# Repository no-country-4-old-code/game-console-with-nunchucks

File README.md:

# Simple Game Console Based on AtMega87-20PU
This is a minimal gaming console based on two AtMega-MCUs.
The input is done via two old "Wii"-Nunchucks.
Output is given via monitor (VGA) and scores are displayed via 7-segment-displays.

The whole thing is rather old (2013), but I had a lot of fun building it.
In other words: Do not expect much regarding clean code etc.

I translate the original documentation into english using AI and put it below.
And yes.. I did a documentation.. but only because this was needed to publish the project on Heise.
The original documentation with all the nice pictures is also in the repo.

## Documentation (Translated by AI)

## Project Overview

This repository documents a simple video game console that runs the classic game **"Pong"** on a standard VGA monitor, controlled by two Wii Nunchuks. The hardware is powered by just two AtMega88-20PU microcontrollers, and the implementation showcases the technical challenges of VGA signal generation and game logic with limited resources.

## Features

**VGA Output**  
The console directly drives a VGA monitor in 640×480 @60Hz mode, outputting all graphics using the AtMega88 microcontroller. The graphics pipeline and Pong gameplay logic are written in Assembler for maximum performance.

**Controller Support**  
Two original Wii Nunchuks serve as input devices. Their joysticks and accelerometers allow paddle control, selectable via board jumpers. Communication is handled via I²C/TWI.

**Score Display**  
An array of four seven-segment displays shows the current score. Multiplexing and updates are managed in C, running on the second AtMega.

**Additional Controls**  
The board features jumpers for color/mode selection, a reset/start button, and three output pins as triggers for a simple sound system (optional, not included).

**Efficient Communication**  
The microcontrollers communicate via a custom UART protocol for fast score and control updates.

## Technical Highlights

### VGA Module

This unit is responsible for image generation, VGA signaling, game mechanics, and data transfer to the controller module. With the VGA protocol being extremely timing-sensitive, the implementation uses Assembler and overclocks the AtMega88 to 22.1145 MHz.  
The software architecture separates graphics generation (run at 5.5 MHz "pixel clock") and game logic into distinct processes, with a timer ISR acting as the scheduler.

### Controller Module

Implemented in C, this module polls the Nunchuks, manages scores, updates the seven-segment displays, and coordinates with the VGA module via UART. Nunchuk polling and game state updates are all performed within a single frame to maintain responsiveness.

### Hardware Design

Most circuit details are derived from the AtMega88 datasheet and well-known application notes (e.g., Philips AN97055 for level shifting). Special consideration is given to transistor pin layouts, with corrective diagrams provided for BC640 and BS108 variants.

## Notes on VGA Implementation

- **Pixel Clock Limitations:** The microcontroller cannot match the standard 25 MHz VGA pixel clock. Instead, output occurs at roughly 5.5 MHz, resulting in horizontally stretched pixels—but reliable display.
- **Memory Handling:** Graphics data is loaded into SRAM at startup for fast access; worklines and images are organized for efficient redrawing of game elements.
- **UART Datagram:** The UART protocol is custom-designed, using 8 data bits, one stop bit, and a baud rate of 32,143 Kbps.

## Images & Schematics

Key diagrams illustrating VGA timing, connector layouts, software architecture, datagram structure, and transistor pinouts are included in the documentation.

---

### Author

**Moritz Koal** (2013)

---

## Caution on Hardware Layout

When assembling, pay close attention to transistor pin assignments—especially for BC640 (swap collector and base) and BS108 (rotate drain and source by 180°). Refer to the included diagrams and datasheets for exact orientation.

---

## License

Feel free to modify, share, and build upon this project for educational or personal use.

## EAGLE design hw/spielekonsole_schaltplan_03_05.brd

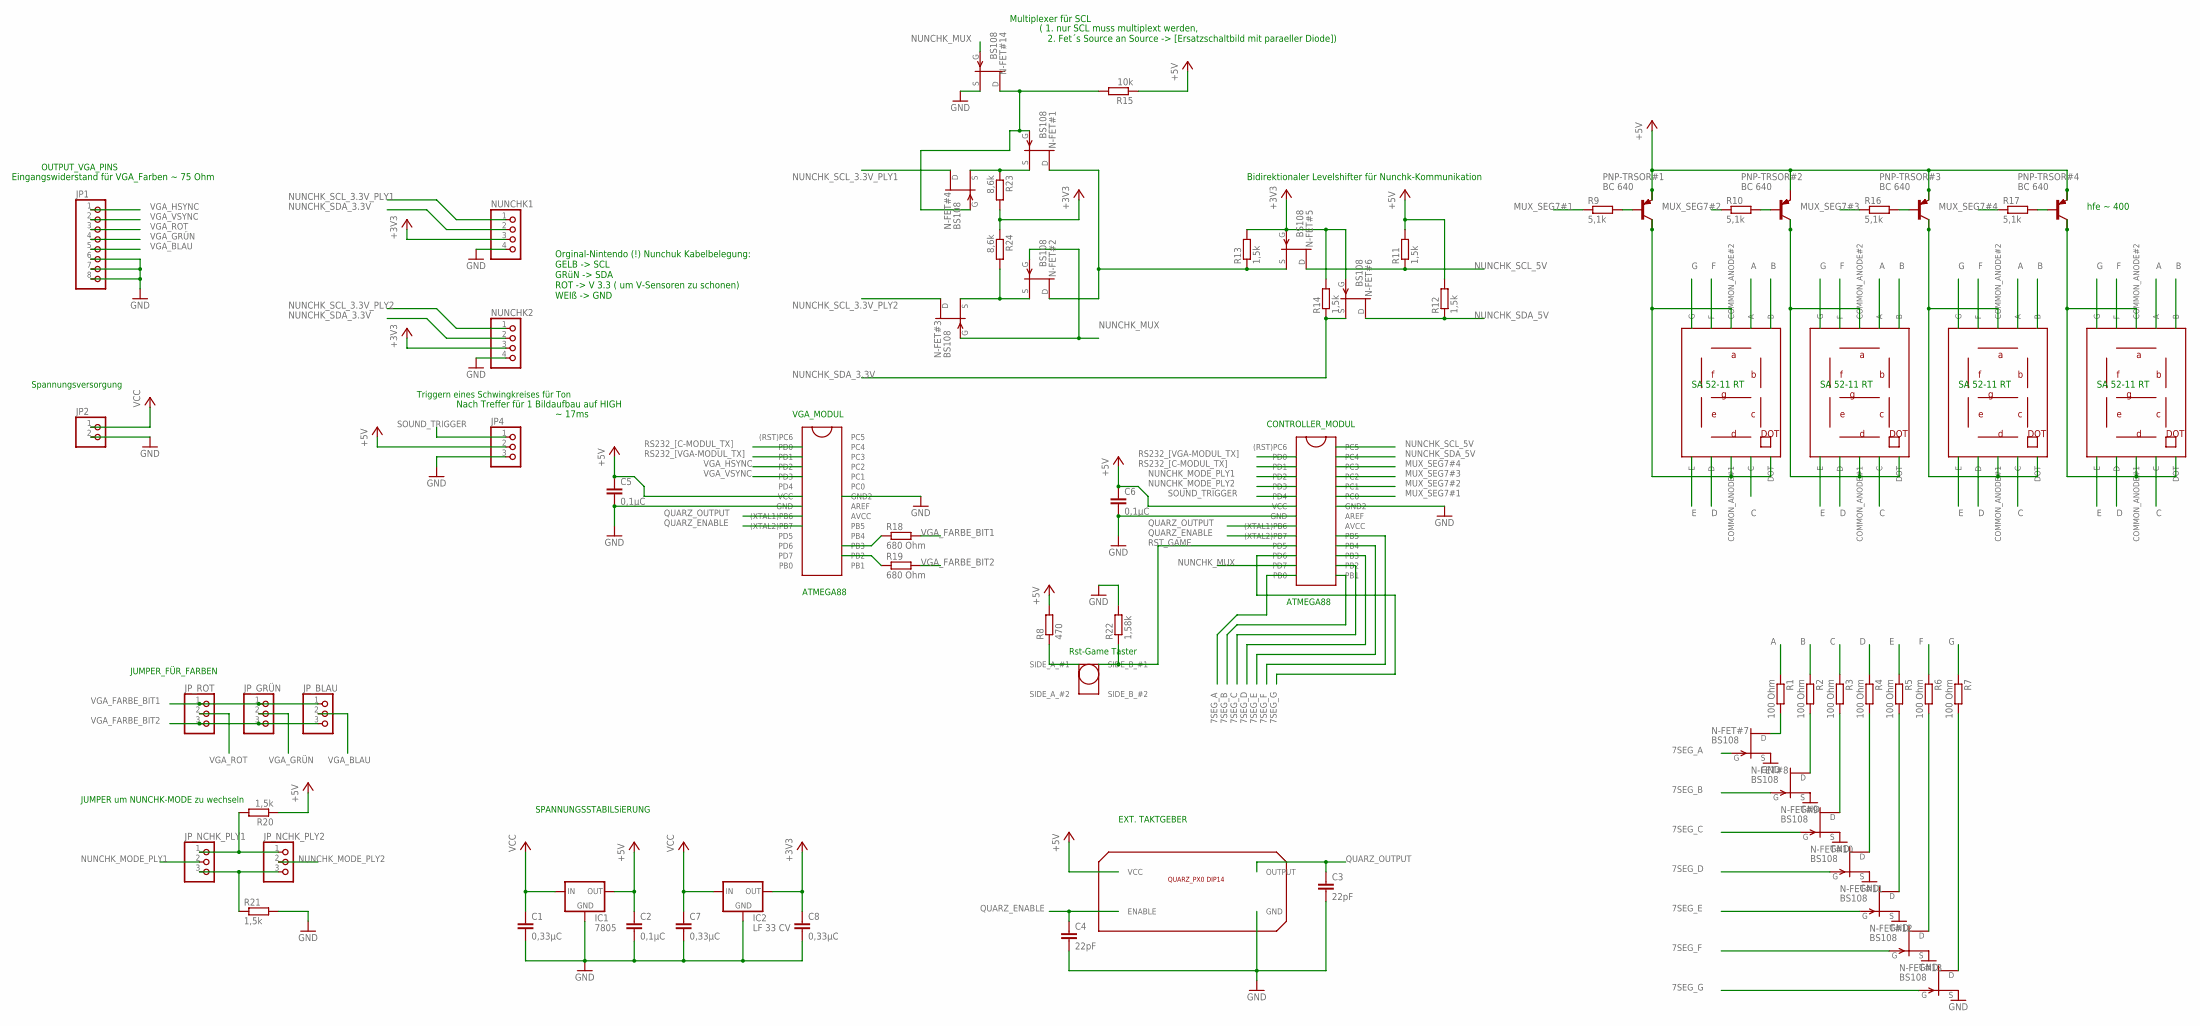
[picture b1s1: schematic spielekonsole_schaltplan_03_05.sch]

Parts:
C1, C7, C8: 0,33µC; C025-024X044
C2, C5, C6: 0,1µC; C025-024X044
C3, C4: 22pF; C025-024X044
IC1: 7805; 78XXL
IC2: LF 33 CV; 78XXL
JP1: PINHD-1X8; 1X08
JP2: PINHD-1X2; 1X02
JP4: PINHD-1X3; 1X03
JP_BLAU: PINHD-1X3; 1X03
JP_GRÜN: PINHD-1X3; 1X03
JP_NCHK_PLY1, JP_NCHK_PLY2: PINHD-1X3; 1X03
JP_ROT: PINHD-1X3; 1X03
N-FET#1, N-FET#2, N-FET#3, N-FET#4, N-FET#5, N-FET#6, N-FET#7, N-FET#8, N-FET#9, N-FET#10, N-FET#11, N-FET#12, N-FET#13, N-FET#14: BS108; TO92
NUNCHK1, NUNCHK2: PINHD-1X4; 1X04
PNP-TRSOR#1, PNP-TRSOR#2, PNP-TRSOR#3, PNP-TRSOR#4: BC 640; TO92-CBE
R1, R2, R3, R4, R5, R6, R7: 100 Ohm; 0204/7
R8: 470; 0204/7
R9, R10, R16, R17: 5,1k; 0204/7
R11, R12, R13, R14, R20, R21: 1,5k; 0204/7
R15: 10k; 0204/7
R18, R19: 680 Ohm; 0204/7
R22: 1,58k; 0204/7
R23, R24: 8,6k; 0204/7
U$1, U$2: ATMEGA 88-20 PU; ATMEGA8_PAC
U$3: QUARZ_PX0_DIP14; QUARZ_PX0_DIP14_PAC
U$4, U$5, U$6, U$7: SA 52-11 RT; SIEBEN_SEG_SA52-11_PAC
U$8: TASTER_1; TASTER_1_PAC

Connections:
7SEG_A: N-FET#7.2 (G), U$2.PB0
7SEG_B: N-FET#8.2 (G), U$2.PB1
7SEG_C: N-FET#9.2 (G), U$2.PB2
7SEG_D: N-FET#10.2 (G), U$2.PB3
7SEG_E: N-FET#11.2 (G), U$2.PB4
7SEG_F: N-FET#12.2 (G), U$2.PB5
7SEG_G: N-FET#13.2 (G), U$2.PD6
+3V3: C8.1, IC2.OUT, N-FET#5.2 (G), N-FET#6.2 (G), NUNCHK1.3, NUNCHK2.3, R13.2, R14.2, R23.2, R24.1
+5V: C2.1, C5.1, C6.1, IC1.OUT, JP4.2, PNP-TRSOR#1.E, PNP-TRSOR#2.E, PNP-TRSOR#3.E, PNP-TRSOR#4.E, R8.2, R11.2, R12.2, R15.1, R20.1, U$1.VCC, U$2.VCC, U$3.VCC
A: R1.1, U$4.A, U$5.A, U$6.A, U$7.A
B: R2.1, U$4.B, U$5.B, U$6.B, U$7.B
C: R3.1, U$4.C, U$5.C, U$6.C, U$7.C
D: R4.1, U$4.D, U$5.D, U$6.D, U$7.D
E: R5.1, U$4.E, U$5.E, U$6.E, U$7.E
ENABLE_SEG7#1: PNP-TRSOR#1.C, U$4.COMMON_ANODE#1, U$4.COMMON_ANODE#2, U$4.DOT
ENABLE_SEG7#2: PNP-TRSOR#2.C, U$5.COMMON_ANODE#1, U$5.COMMON_ANODE#2, U$5.DOT
ENABLE_SEG7#3: PNP-TRSOR#3.C, U$6.COMMON_ANODE#1, U$6.COMMON_ANODE#2, U$6.DOT
ENABLE_SEG7#4: PNP-TRSOR#4.C, U$7.COMMON_ANODE#1, U$7.COMMON_ANODE#2, U$7.DOT
F: R6.1, U$4.F, U$5.F, U$6.F, U$7.F
G: R7.1, U$4.G, U$5.G, U$6.G, U$7.G
GND: C1.2, C2.2, C3.2, C4.2, C5.2, C6.2, C7.2, C8.2, IC1.GND, IC2.GND, JP1.6, JP1.7, JP1.8, JP2.2, JP4.3, N-FET#7.3 (S), N-FET#8.3 (S), N-FET#9.3 (S), N-FET#10.3 (S), N-FET#11.3 (S), N-FET#12.3 (S), N-FET#13.3 (S), N-FET#14.3 (S), NUNCHK1.4, NUNCHK2.4, R21.2, R22.2, U$1.GND1 (GND), U$1.GND2, U$2.GND1 (GND), U$2.GND2, U$3.GND
MUX_SEG7#1: R9.1, U$2.PC0
MUX_SEG7#2: R10.1, U$2.PC1
MUX_SEG7#3: R16.1, U$2.PC2
MUX_SEG7#4: R17.1, U$2.PC3
unnamed: R8.1, U$8.SIDE_A_#1
unnamed: PNP-TRSOR#1.B, R9.2
unnamed: PNP-TRSOR#2.B, R10.2
unnamed: PNP-TRSOR#3.B, R16.2
unnamed: PNP-TRSOR#4.B, R17.2
unnamed: R18.1, U$1.PB3
unnamed: R19.1, U$1.PB2
unnamed: JP_NCHK_PLY1.3, JP_NCHK_PLY2.3, R21.1
unnamed: N-FET#1.2 (G), N-FET#4.2 (G), N-FET#14.1 (D), R15.2
unnamed: JP_NCHK_PLY1.1, JP_NCHK_PLY2.1, R20.2
unnamed: N-FET#1.1 (D), N-FET#2.1 (D), N-FET#5.3 (S), R13.1
unnamed: N-FET#1.3 (S), N-FET#4.3 (S), R23.1
unnamed: N-FET#2.3 (S), N-FET#3.3 (S), R24.2
unnamed: N-FET#7.1 (D), R1.2
unnamed: N-FET#8.1 (D), R2.2
unnamed: N-FET#9.1 (D), R3.2
unnamed: N-FET#10.1 (D), R4.2
unnamed: N-FET#11.1 (D), R5.2
unnamed: N-FET#12.1 (D), R6.2
unnamed: N-FET#13.1 (D), R7.2
NUNCHK_MODE_PLY1: JP_NCHK_PLY1.2, U$2.PD2
NUNCHK_MODE_PLY2: JP_NCHK_PLY2.2, U$2.PD3
NUNCHK_MUX: N-FET#2.2 (G), N-FET#3.2 (G), N-FET#14.2 (G), U$2.PD7
NUNCHK_SCL_3.3V_PLY1: N-FET#4.1 (D), NUNCHK1.1
NUNCHK_SCL_3.3V_PLY2: N-FET#3.1 (D), NUNCHK2.1
NUNCHK_SCL_5V: N-FET#5.1 (D), R11.1, U$2.PC5
NUNCHK_SDA_3.3V: N-FET#6.3 (S), NUNCHK1.2, NUNCHK2.2, R14.1
NUNCHK_SDA_5V: N-FET#6.1 (D), R12.1, U$2.PC4
QUARZ_ENABLE: C4.1, U$1.PB7 ((XTAL2)PB7), U$2.PB7 ((XTAL2)PB7), U$3.ENABLE
QUARZ_OUTPUT: C3.1, U$1.PB6 ((XTAL1)PB6), U$2.PB6 ((XTAL1)PB6), U$3.OUTPUT
RS232_[C-MODUL_TX]: U$1.PD0, U$2.PD1
RS232_[VGA-MODUL_TX]: U$1.PD1, U$2.PD0
RST_GAME: R22.1, U$2.PD5, U$8.SIDE_B_#1
SOUND_TRIGGER: JP4.1, U$2.PD4
VCC: C1.1, C7.1, IC1.IN, IC2.IN, JP2.1
VGA_BLAU: JP1.5, JP_BLAU.2
VGA_FARBE_BIT1: JP_BLAU.1, JP_GRÜN.1, JP_ROT.1, R18.2
VGA_FARBE_BIT2: JP_BLAU.3, JP_GRÜN.3, JP_ROT.3, R19.2
VGA_GRÜN: JP1.4, JP_GRÜN.2
VGA_HSYNC: JP1.1, U$1.PD2
VGA_ROT: JP1.3, JP_ROT.2
VGA_VSYNC: JP1.2, U$1.PD3

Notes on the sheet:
OUTPUT_VGA_PINS
JUMPER_FÜR_FARBEN
VGA_MODUL
SPANNUNGSSTABILSiERUNG
Spannungsversorgung
EXT. TAKTGEBER
CONTROLLER_MODUL
ATMEGA88
JUMPER um NUNCHK-MODE zu wechseln
Triggern eines Schwingkreises für Ton
Rst-Game Taster
Orginal-Nintendo (!) Nunchuk Kabelbelegung: GELB -> SCL GRüN -> SDA ROT -> V 3.3 ( um V-Sensoren zu schonen) WEIß -> GND
Multiplexer für SCL
Bidirektionaler Levelshifter für Nunchk-Kommunikation
hfe ~ 400
Eingangswiderstand für VGA_Farben ~ 75 Ohm
Nach Treffer für 1 Bildaufbau auf HIGH
~ 17ms
( 1. nur SCL muss multiplext werden, 2. Fet´s Source an Source -> [Ersatzschaltbild mit paraeller Diode])
SA 52-11 RT

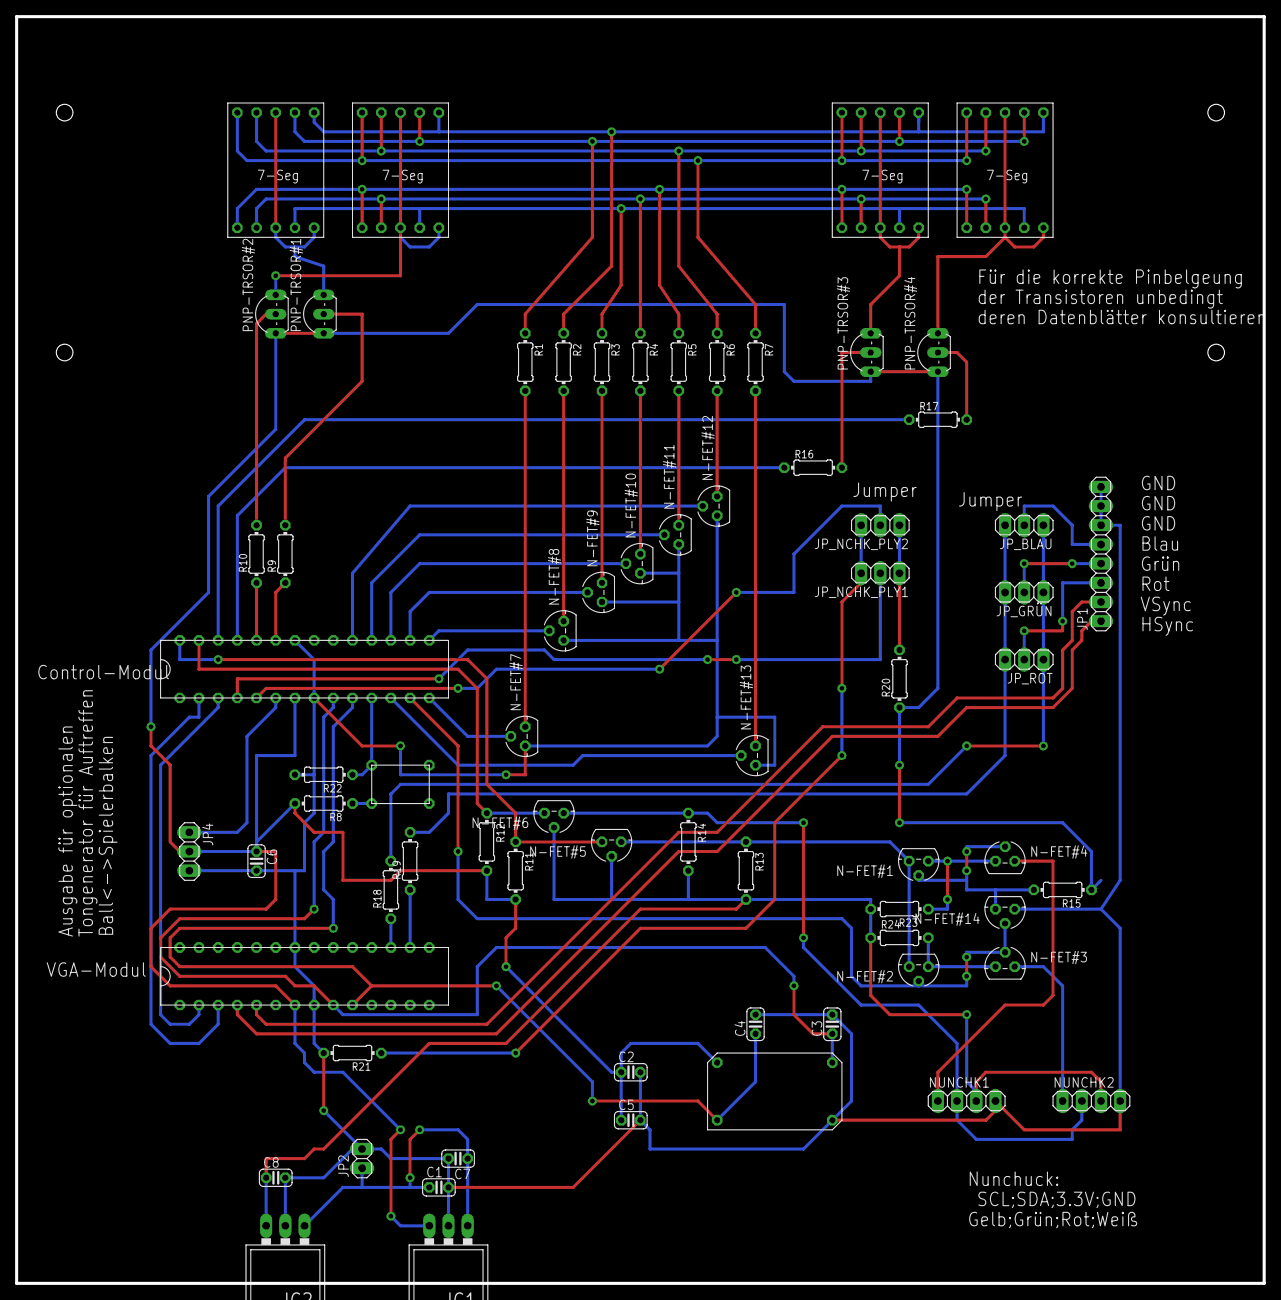
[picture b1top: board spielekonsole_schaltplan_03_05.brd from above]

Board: 2 copper layers, 165.1 x 167.6 mm, 70 parts (0 on the bottom side), 67 nets.

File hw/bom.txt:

Stückliste

//======== Eagle

Qty Value            Device             Package                Parts                                                                                                                             Description                
1                    PINHD-1X2          1X02                   JP2                                                                                                                               PIN HEADER                 
6                    PINHD-1X3          1X03                   JP4, JP_BLAU, JP_GRÜN, JP_NCHK_PLY1, JP_NCHK_PLY2, JP_ROT                                                                         PIN HEADER                 
2                    PINHD-1X4          1X04                   NUNCHK1, NUNCHK2                                                                                                                  PIN HEADER                 
1                    PINHD-1X8          1X08                   JP1                                                                                                                               PIN HEADER                 
3   0,1µC            C-EU025-024X044    C025-024X044           C2, C5, C6                                                                                                                        CAPACITOR, European symbol 
3   0,33µC           C-EU025-024X044    C025-024X044           C1, C7, C8                                                                                                                        CAPACITOR, European symbol 
1   1,58k            R-EU_0204/7        0204/7                 R22                                                                                                                               RESISTOR, European symbol  
6   1,5k             R-EU_0204/7        0204/7                 R11, R12, R13, R14, R20, R21                                                                                                      RESISTOR, European symbol  
7   100 Ohm          R-EU_0204/7        0204/7                 R1, R2, R3, R4, R5, R6, R7                                                                                                        RESISTOR, European symbol  
1   10k              R-EU_0204/7        0204/7                 R15                                                                                                                               RESISTOR, European symbol  
2   22pF             C-EU025-024X044    C025-024X044           C3, C4                                                                                                                            CAPACITOR, European symbol 
1   470              R-EU_0204/7        0204/7                 R8                                                                                                                                RESISTOR, European symbol  
4   5,1k             R-EU_0204/7        0204/7                 R9, R10, R16, R17                                                                                                                 RESISTOR, European symbol  
2   680 Ohm          R-EU_0204/7        0204/7                 R18, R19                                                                                                                          RESISTOR, European symbol  
1   7805             78XXL              78XXL                  IC1                                                                                                                               VOLTAGE REGULATOR          
2   8,6k             R-EU_0204/7        0204/7                 R23, R24                                                                                                                          RESISTOR, European symbol  
2   ATMEGA 88-20 PU  ATMEGA8            ATMEGA8_PAC            U$1, U$2                                                                                                                                                     
4   BC 640           2N4126             TO92-CBE               PNP-TRSOR#1, PNP-TRSOR#2, PNP-TRSOR#3, PNP-TRSOR#4                                                                                PNP Transistror            
14  BS108            2N3819             TO92                   N-FET#1, N-FET#2, N-FET#3, N-FET#4, N-FET#5, N-FET#6, N-FET#7, N-FET#8, N-FET#9, N-FET#10, N-FET#11, N-FET#12, N-FET#13, N-FET#14 N-Channel Junction FET     
1   LF 33 CV         78XXL              78XXL                  IC2                                                                                                                               VOLTAGE REGULATOR          
1   QUARZ_PX0_DIP14  QUARZ_PX0_DIP14    QUARZ_PX0_DIP14_PAC    U$3                                                                                                                                                          
4   SA 52-11 RT      SIEBEN_SEG_SA52-11 SIEBEN_SEG_SA52-11_PAC U$4, U$5, U$6, U$7                                                                                                                                           
1   TASTER_1         TASTER_1           TASTER_1_PAC           U$8                                                                                                                                                          

//========== Sonstiges 

2  *	GS 28P-S		IC-Sockel für Atmega88
5  *	MPE 087-1-003		Stiftleisten mit 2,54mm ( für Jumper )
5  *	Jumper 2,54mm		Zur Auswahl Joystick/Beschleunigungssensor etc
8  *	MPE 094-1-005		Buchsenleiste,1X05 2,54mm für Siebensegment Blöcke
4  *	MPE 094-1-004		Buchsenleiste,1X04 2,54mm für Quarz und Nunchucks
2  *	MPE 087-1-004		Stiftleiste,1X04 2,54mm für Nunchucks ( Besser wäre natürlich ein Adapter, so dass man die Nunchucks nicht aufschneiden muss )
1  *	Tastschalter + gegebenfalls entsprechende Buchsenleisten ( z.B. FSM2JH + 2* MPE 094-1-003 )
1  * 	DELOCK 65170		16 Pin, VGA-Buchse <-> Terminalblock. ( Erleichtert den Anschluss )

//========== Stromversorgung
1  *	PSAA 18U-090		Kompaktschaltnetzteil , 18 W , 9 V out
1  *	HEBFL 21		Hohlstecker-Einbaubuchse, Flansch, Stift 2,1mm

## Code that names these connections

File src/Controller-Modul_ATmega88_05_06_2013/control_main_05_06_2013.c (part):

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#define RST_PORT PORTD
#define RST_PINS PIND
#define RST_DDR DDRD
#define RST_PIN PD5
#define RST_ACTIV 1 // High Aktiv

// Watchdog
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#define NUNCHK_MODE_PORT PORTD
#define NUNCHK_MODE_PINS PIND
#define NUNCHK_MODE_DDR DDRD
#define NUNCHK_MODE_PIN_PLY1 PD2
#define NUNCHK_MODE_PIN_PLY2 PD3
#define NUNCHK_MODE_STICK 1
#define NUNCHK_MODE_VSENSOR 0
#define NUNCHK_MODE_STICK_SEGMENT 0
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// 'Pong'-Ton Ausgabe
#define SOUND_PORT PORTD
#define SOUND_DDR DDRD
#define SOUND_PIN PD4
#define SOUND_AKTIV 1 // immer über einen Zyklus (also ~ 1/60 s aktiv -> außer beim aufhängen .... ) -> abfange routine in Timer-ISR

// SiebenSeg
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#define SEG7_OUTPUT2_PORT PORTD
#define SEG7_OUTPUT1_DDR DDRB
#define SEG7_OUTPUT2_DDR DDRD
#define SEG7_OUTPUT_PINS1  0b00111111//(1<<PB0)|(1<<PB1)|(1<<PB2)|(1<<PB3)|(1<<PB4)|(1<<PB5)  //0b00111111 // PB0 bis PB5
#define SEG7_OUTPUT_PINS2  0b01000000//(1<< PD6)  //0b01000000 // PD6 als 7ter Pin
#define NUM_OF_SEG7_DISPLAYS 4
#define NUM_OF_NUMBERS4DISPLAY 10 // Bei Änderung das Array "seg7_umwandlung_zahl2seg7" anpassen !

#define SEG7_MUX_PORT PORTC
#define SEG7_MUX_DDR DDRC
#define SEG7_MUX_PINS 0x0F // PC3:PC0

//Timer0
#define TIMER0_PRESCALER 0x05
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#define NUM_OF_NUNCHK_DATA 6

// Für Nunchuck Multiplexer
#define MULTI_NUCHK_PIN PD7
#define MULTIPLI_NUCHK_PORT PORTD
#define MULTIPLI_NUCHK_DDR DDRD
#define TIME_AFTER_CHANGE_NUCHK_us 1
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volatile uint8_t watchdog_counter=0; //Reagiert wenn lange keine RSR232-ISR mehr ausgeführt wurde, um Deadlock zu verhindern. 
uint8_t volatile seg7_zahlenwerte[NUM_OF_SEG7_DISPLAYS]={1,2,3,4}; // die jeweiligen Zahlenwerte ,die angezeigt werden sollen ( 1:0 [Player1] ; 3:2 [Player2] )
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uint8_t volatile seg7_multiplex_werte[NUM_OF_SEG7_DISPLAYS]={0x07,0x0B,0x0D,0x0E}; // PC3:PC0 // LOW Aktiv



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	SEG7_OUTPUT1_PORT=tmp;
	tmp=SEG7_OUTPUT2_PORT;
	tmp&=~SEG7_OUTPUT_PINS2;
	tmp|=(seg7_umwandlung_zahl2seg7[seg7_zahlenwerte[seg7_aktive_anzeige]]&SEG7_OUTPUT_PINS2); // geht weil PD6 genau das 7ze Bit deckt (ansosnten noch zusätzliche SchiebeOP)
	SEG7_OUTPUT2_PORT=tmp;
}
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
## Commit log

2026-01-13 Add readme
2026-01-13 add docs, hw, media, src under version control
2026-01-13 Add image and clarify documentation in README
    Added an image to the README and clarified documentation source.
2026-01-13 add MIT license
